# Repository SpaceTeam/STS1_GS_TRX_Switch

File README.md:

# Ground Station TRX Switch

This boards provides sequencing and switching for transmit and receive path of a satellite groundstation based on two galvanically isolated inputs.  
It features an on-board LNA with filter and pre and post filtering for an external power amplifier.  
It also provides ~30V switched for the PA derived from one common 48V supply.

It is controlled by an Arduino Nano which is used for timing.
It features two high-side MOSFET outputs for enabling a PA and LNA and three coaxial relays for RX/TX switching and antenna grounding (when neither RX nor TX is enabled).

The design was built for around 435MHz but probably is easy to adapt to different frequencies up to 3GHz.

## Ordering

The RF design is built for the "standard" 1.6mm thick JLCPCB 4-layer stackup consisting of the following layers:
- 35µm Outer copper
- 210.4µm Prepreg (7628, RC 49%, 8.6mil)
- 15.2µm Inner copper
- 1.065mm Core
- 15.2µm Inner copper
- 210.4µm Prepreg (7628, RC 49%, 8.6mil)
- 35µm Outer copper

For finish please choose ENIG.

## License
All files in this repository are licensed under the MIT license EXCEPT for the files in the `/3d` directory.

- Arduino Nano: By Andrew Whitham (https://grabcad.com/library/arduino-nano--1), noncommercial public use allowed (https://help.grabcad.com/article/246-how-can-models-be-used-and-shared?locale=en)
- TE HF3-53: Copyright TE Connectivity (https://www.te.com/usa-en/product-1462051-2.html)
- Molex 73251-2120: Copyright Molex LLC (https://www.molex.com/en-us/products/part-detail/0732512120)

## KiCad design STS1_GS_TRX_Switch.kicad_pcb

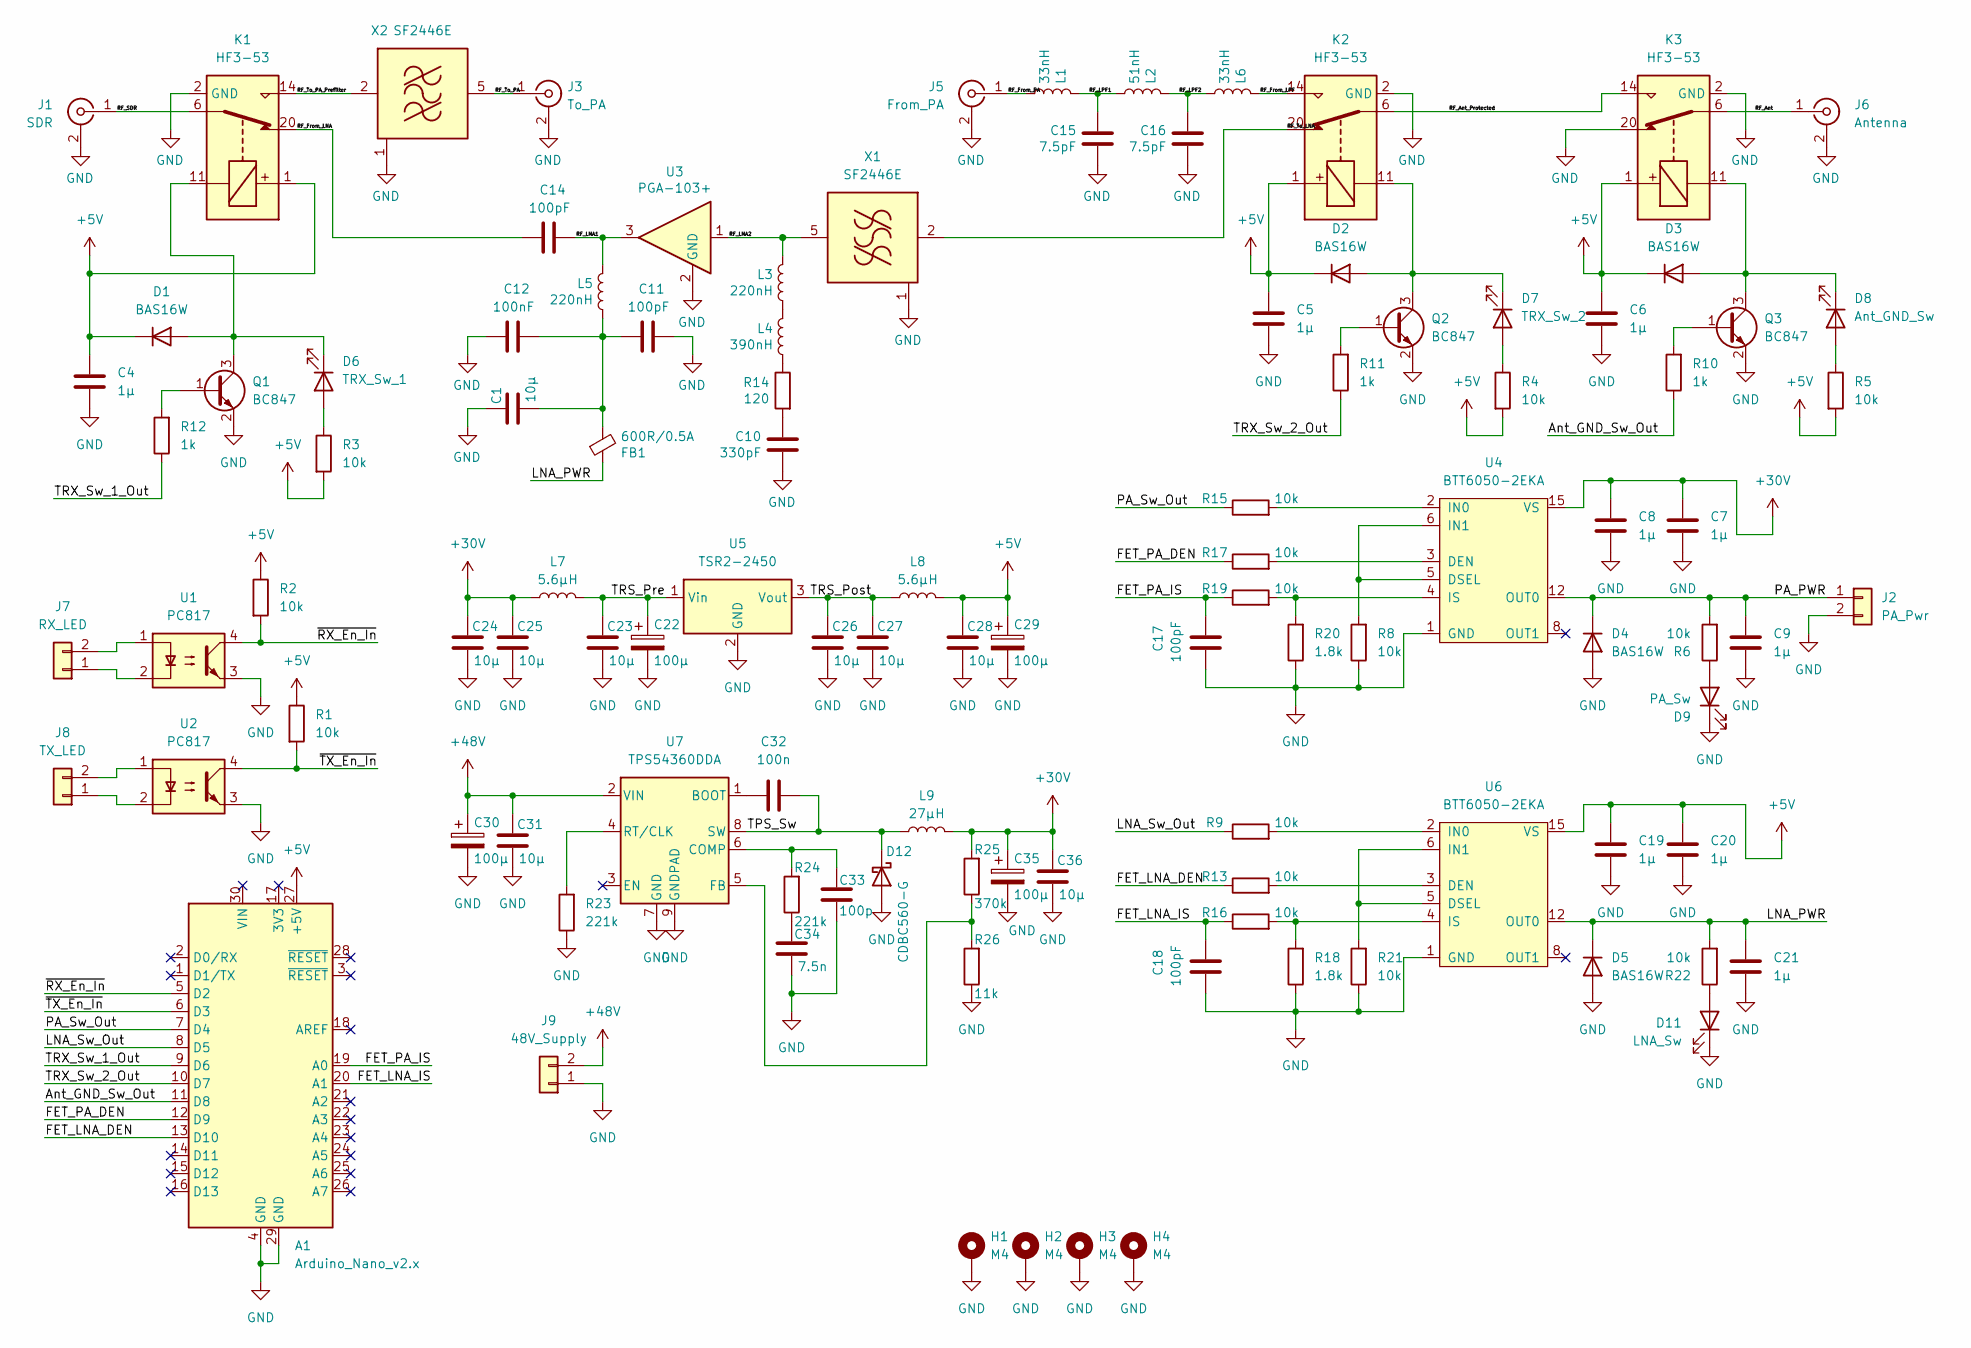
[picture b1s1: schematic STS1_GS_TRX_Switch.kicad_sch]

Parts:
A1: Arduino_Nano_v2.x; Arduino_Nano
C1, C24, C25, C36: 10µ; C_1210_3225Metric_Pad1.33x2.70mm_HandSolder
C4, C5, C6, C7, C8, C9, C19, C20, C21: 1µ; C_0603_1608Metric_Pad1.08x0.95mm_HandSolder
C10: 330pF; C_0603_1608Metric
C11, C14, C17, C18: 100pF; C_0603_1608Metric
C12: 100nF; C_0603_1608Metric
C15, C16: 7.5pF; C_0603_1608Metric
C22, C29, C30, C35: 100µ; CP_Elec_10x10
C23, C26, C27, C28, C31: 10µ; C_0805_2012Metric_Pad1.18x1.45mm_HandSolder
C32: 100n; C_0805_2012Metric_Pad1.18x1.45mm_HandSolder
C33: 100p; C_0603_1608Metric_Pad1.08x0.95mm_HandSolder
C34: 7.5n; C_1206_3216Metric_Pad1.33x1.80mm_HandSolder
D1, D2, D3, D4, D5: BAS16W; SOT-323_SC-70
D6: TRX_Sw_1; LED_1206_3216Metric_Pad1.42x1.75mm_HandSolder
D7: TRX_Sw_2; LED_1206_3216Metric_Pad1.42x1.75mm_HandSolder
D8: Ant_GND_Sw; LED_1206_3216Metric_Pad1.42x1.75mm_HandSolder
D9: PA_Sw; LED_1206_3216Metric_Pad1.42x1.75mm_HandSolder
D11: LNA_Sw; LED_1206_3216Metric_Pad1.42x1.75mm_HandSolder
D12: CDBC560-G; D_SMC_Handsoldering; MPN CDBC560-G
FB1: 600R/0.5A; Murata-BLM18-0.15-t0.8-0-0-IPC_A
H1, H2, H3, H4: M4; MountingHole_4.3mm_M4_Pad_Via
J1: SDR; SMA_Molex_73251-2120_EdgeMount_Horizontal
J2: PA_Pwr; JST_XH_B2B-XH-A_1x02_P2.50mm_Vertical
J3: To_PA; SMA_Molex_73251-2120_EdgeMount_Horizontal
J5: From_PA; SMA_Molex_73251-2120_EdgeMount_Horizontal
J6: Antenna; SMA_Molex_73251-2120_EdgeMount_Horizontal
J7: RX_LED; PhoenixContact_MSTBA_2,5_2-G-5,08_1x02_P5.08mm_Horizontal
J8: TX_LED; PhoenixContact_MSTBA_2,5_2-G-5,08_1x02_P5.08mm_Horizontal
J9: 48V_Supply; PhoenixContact_MSTBA_2,5_2-G-5,08_1x02_P5.08mm_Horizontal
K1, K2, K3: HF3-53; Relay_SPDT_AXICOM_HF3Series_50ohms_Pitch1.27mm
L1, L6: 33nH; L_0603_1608Metric_Pad1.05x0.95mm_HandSolder; MPN LQW18AN33NJ80D
L2: 51nH; L_0603_1608Metric_Pad1.05x0.95mm_HandSolder; MPN LQW18AN51NG80D
L3, L5: 220nH; L_0805_2012Metric; MPN LQW2BASR22J00L
L4: 390nH; L_0805_2012Metric; MPN LQW2BASR39J00L
L7, L8: 5.6µH; L_Abracon_ASPI-4030S; MPN ASPI-4030S-5R6M-T
L9: 27µH; L_Bourns_SRR1210A; MPN SRR1210-270M
Q1, Q2, Q3: BC847; SOT-23
R1, R2, R3, R4, R5, R6, R8, R9, R13, R15, R16, R17, R19, R21, R22: 10k; R_0603_1608Metric_Pad0.98x0.95mm_HandSolder
R10, R11, R12: 1k; R_0603_1608Metric_Pad0.98x0.95mm_HandSolder
R14: 120; R_0603_1608Metric
R18, R20: 1.8k; R_0603_1608Metric_Pad0.98x0.95mm_HandSolder
R23, R24: 221k; R_0603_1608Metric_Pad0.98x0.95mm_HandSolder
R25: 370k; R_0603_1608Metric_Pad0.98x0.95mm_HandSolder
R26: 11k; R_0603_1608Metric_Pad0.98x0.95mm_HandSolder
U1, U2: PC817; DIP-4_W7.62mm
U3: PGA-103+; SOT-89-3
U4, U6: BTT6050-2EKA; Infineon_PG-DSO-14-40-EP_3.9x8.65mm_P1.27mm
U5: TSR2-2450; Converter_DCDC_TRACO_TSR2-xxxx_THT
U7: TPS54360DDA; TI_SO-PowerPAD-8_ThermalVias
X1, X2: SF2446E; Filter_SAW-6_3.0x3.0mm

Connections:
+5V: A1.27 (+5V), C4.1, C5.1, C6.1, C19.1, C20.1, C28.1, C29.1, D1.3 (K), D2.3 (K), D3.3 (K), K1.1, K2.1, K3.1, L8.2, R1.1, R2.1, R3.2, R4.2, R5.2, U6.15 (VS)
+30V: C7.1, C8.1, C24.1, C25.1, C35.1, C36.1, L7.1, L9.2, R25.2, U4.15 (VS)
+48V: C30.1, C31.1, J9.2, U7.2 (VIN)
/Ant_GND_Sw_Out: A1.11 (D8), R10.1
/FET_LNA_DEN: A1.13 (D10), R13.1
/FET_LNA_IS: A1.20 (A1), C18.1, R16.1
/FET_PA_DEN: A1.12 (D9), R17.1
/FET_PA_IS: A1.19 (A0), C17.1, R19.1
/LNA_PWR: C21.1, D5.3 (K), FB1.1, R22.2, U6.12 (OUT0), U6.13 (OUT0), U6.14 (OUT0)
/LNA_Sw_Out: A1.8 (D5), R9.1
/PA_PWR: C9.1, D4.3 (K), J2.1, R6.2, U4.12 (OUT0), U4.13 (OUT0), U4.14 (OUT0)
/PA_Sw_Out: A1.7 (D4), R15.1
/RF_Ant: J6.1 (In), K3.6
/RF_Ant_Protected: K2.6, K3.14
/RF_From_LNA: C14.2, K1.20
/RF_From_LPF: K2.14, L6.1
/RF_From_PA: J5.1 (In), L1.2
/RF_LNA1: C14.1, L5.1, U3.3
/RF_LNA2: L3.1, U3.1, X1.5 (OUT)
/RF_LPF1: C15.1, L1.1, L2.2
/RF_LPF2: C16.1, L2.1, L6.2
/RF_SDR: J1.1 (In), K1.6
/RF_To_LNA: K2.20, X1.2 (IN)
/RF_To_PA: J3.1 (In), X2.5 (OUT)
/RF_To_PA_Prefilter: K1.14, X2.2 (IN)
/TPS_Sw: C32.2, D12.1 (K), L9.1, U7.8 (SW)
/TRS_Post: C26.1, C27.1, L8.1, U5.3 (Vout)
/TRS_Pre: C22.1, C23.1, L7.2, U5.1 (Vin)
/TRX_Sw_1_Out: A1.9 (D6), R12.1
/TRX_Sw_2_Out: A1.10 (D7), R11.1
/~RX_En_In: A1.5 (D2), R2.2, U1.4
/~TX_En_In: A1.6 (D3), R1.2, U2.4
GND: A1.4 (GND), A1.29 (GND), C1.1, C4.2, C5.2, C6.2, C7.2, C8.2, C9.2, C10.2, C11.1, C12.2, C15.2, C16.2, C17.2, C18.2, C19.2, C20.2, C21.2, C22.2, C23.2, C24.2, C25.2, C26.2, C27.2, C28.2, C29.2, C30.2, C31.2, C33.2, C34.2, C35.2, C36.2, D4.1 (A), D5.1 (A), D9.1 (K), D11.1 (K), D12.2 (A), H1.1, H2.1, H3.1, H4.1, J1.2 (Ext), J2.2, J3.2 (Ext), J5.2 (Ext), J6.2 (Ext), J9.1, K1.2 (GND), K1.5 (GND), K1.7 (GND), K1.10 (GND), K1.12 (GND), K1.13 (GND), K1.15 (GND), K1.17 (GND), K1.19 (GND), K1.21 (GND), K1.22 (GND), K2.2 (GND), K2.5 (GND), K2.7 (GND), K2.10 (GND), K2.12 (GND), K2.13 (GND), K2.15 (GND), K2.17 (GND), K2.19 (GND), K2.21 (GND), K2.22 (GND), K3.2 (GND), K3.5 (GND), K3.7 (GND), K3.10 (GND), K3.12 (GND), K3.13 (GND), K3.15 (GND), K3.17 (GND), K3.19 (GND), K3.20, K3.21 (GND), K3.22 (GND), Q1.2 (E), Q2.2 (E), Q3.2 (E), R8.1, R18.1, R20.1, R21.1, R23.1, R26.1, U1.3, U2.3, U3.2 (GND), U4.1 (GND), U5.2 (GND), U6.1 (GND), U7.7 (GND), U7.9 (GNDPAD), X1.1 (GND), X1.3 (GND), X1.4 (GND), X1.6 (GND), X2.1 (GND), X2.3 (GND), X2.4 (GND), X2.6 (GND)
unnamed: C1.2, C11.2, C12.1, FB1.2, L5.2
unnamed: C10.1, R14.2
unnamed: C34.1, R24.1
unnamed: D1.1 (A), D6.1 (K), K1.11, Q1.3 (C)
unnamed: D2.1 (A), D7.1 (K), K2.11, Q2.3 (C)
unnamed: D3.1 (A), D8.1 (K), K3.11, Q3.3 (C)
unnamed: D6.2 (A), R3.1
unnamed: D7.2 (A), R4.1
unnamed: D8.2 (A), R5.1
unnamed: D9.2 (A), R6.1
unnamed: D11.2 (A), R22.1
unnamed: J7.1, U1.2
unnamed: J7.2, U1.1
unnamed: J8.1, U2.2
unnamed: J8.2, U2.1
unnamed: L3.2, L4.1
unnamed: L4.2, R14.1
unnamed: Q1.1 (B), R12.2
unnamed: Q2.1 (B), R11.2
unnamed: Q3.1 (B), R10.2
unnamed: R17.2, U4.3 (DEN)
unnamed: R8.2, U4.5 (DSEL), U4.6 (IN1)
unnamed: R15.2, U4.2 (IN0)
unnamed: R19.2, R20.2, U4.4 (IS)
unnamed: R13.2, U6.3 (DEN)
unnamed: R21.2, U6.5 (DSEL), U6.6 (IN1)
unnamed: R9.2, U6.2 (IN0)
unnamed: R16.2, R18.2, U6.4 (IS)
unnamed: C32.1, U7.1 (BOOT)
unnamed: C33.1, R24.2, U7.6 (COMP)
unnamed: R25.1, R26.2, U7.5 (FB)
unnamed: R23.2, U7.4 (RT/CLK)

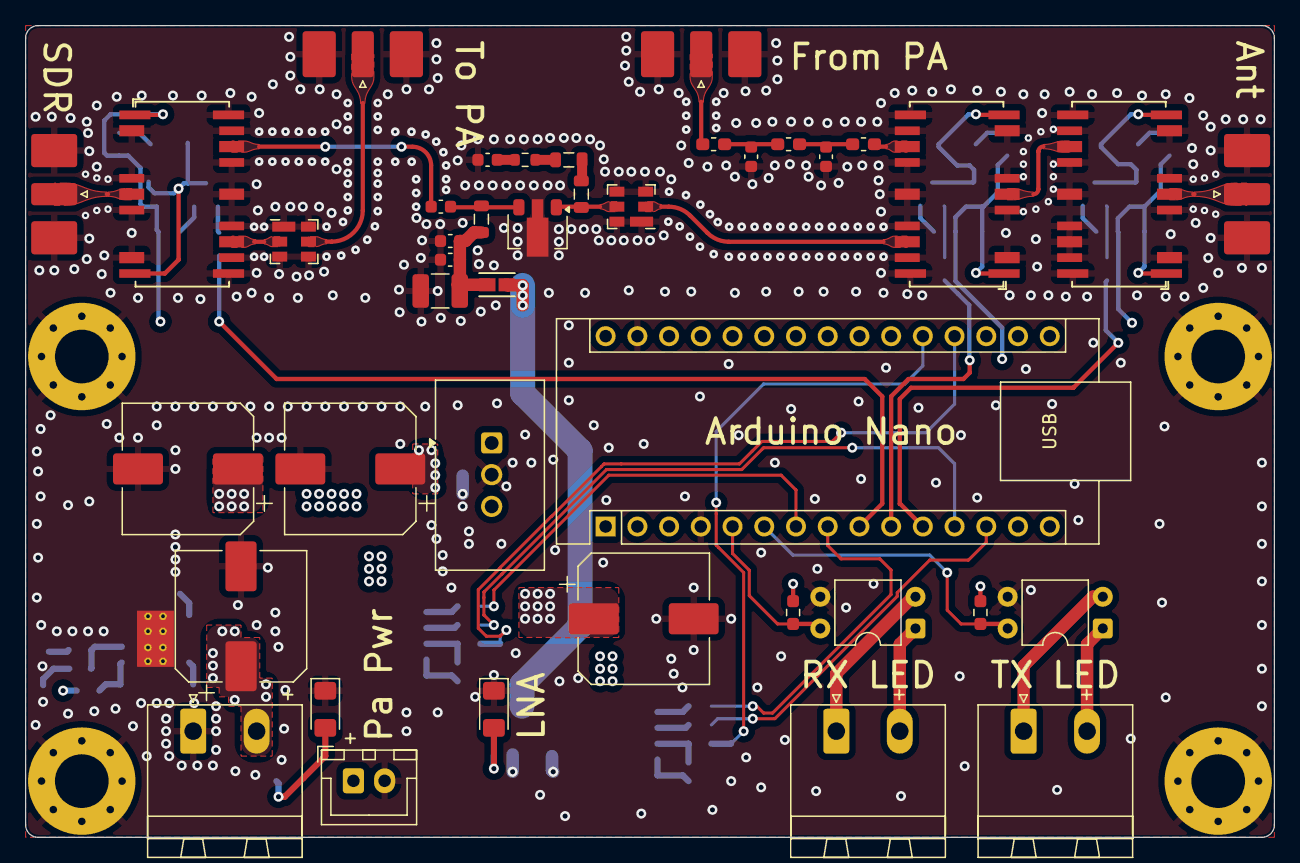
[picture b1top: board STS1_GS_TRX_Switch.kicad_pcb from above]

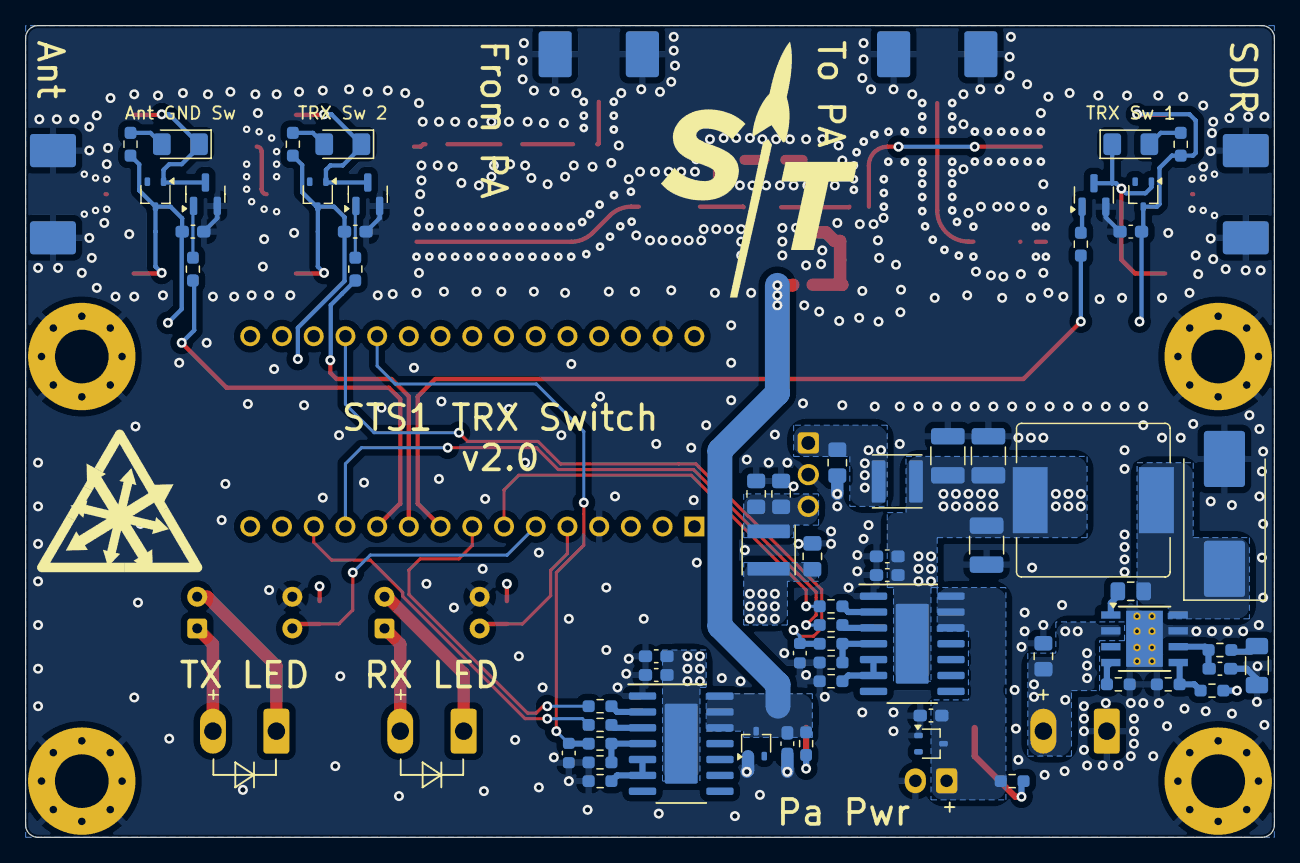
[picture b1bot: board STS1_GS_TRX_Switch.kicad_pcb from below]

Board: 4 copper layers, 100.0 x 65.0 mm, 107 parts (62 on the bottom side), 65 nets.

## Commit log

2023-10-06 feat: initial commit
2023-10-06 feat: add MIT license
2023-10-06 feat: improve readme
2023-10-06 feat: clarify finish
2023-10-06 fix: Logo was flipped
2025-06-14 fix: wrong polarity of one of the RF relays
2025-09-16 feat: v2.0 with built-in LNA, PA-pre-filter and PA output filter
2025-09-16 feat: update README for v2.0
2025-10-09 feat: add arduino sketch
2025-10-26 fix: increase delays to prevent LNA from oscillating on turn on because of an open input
